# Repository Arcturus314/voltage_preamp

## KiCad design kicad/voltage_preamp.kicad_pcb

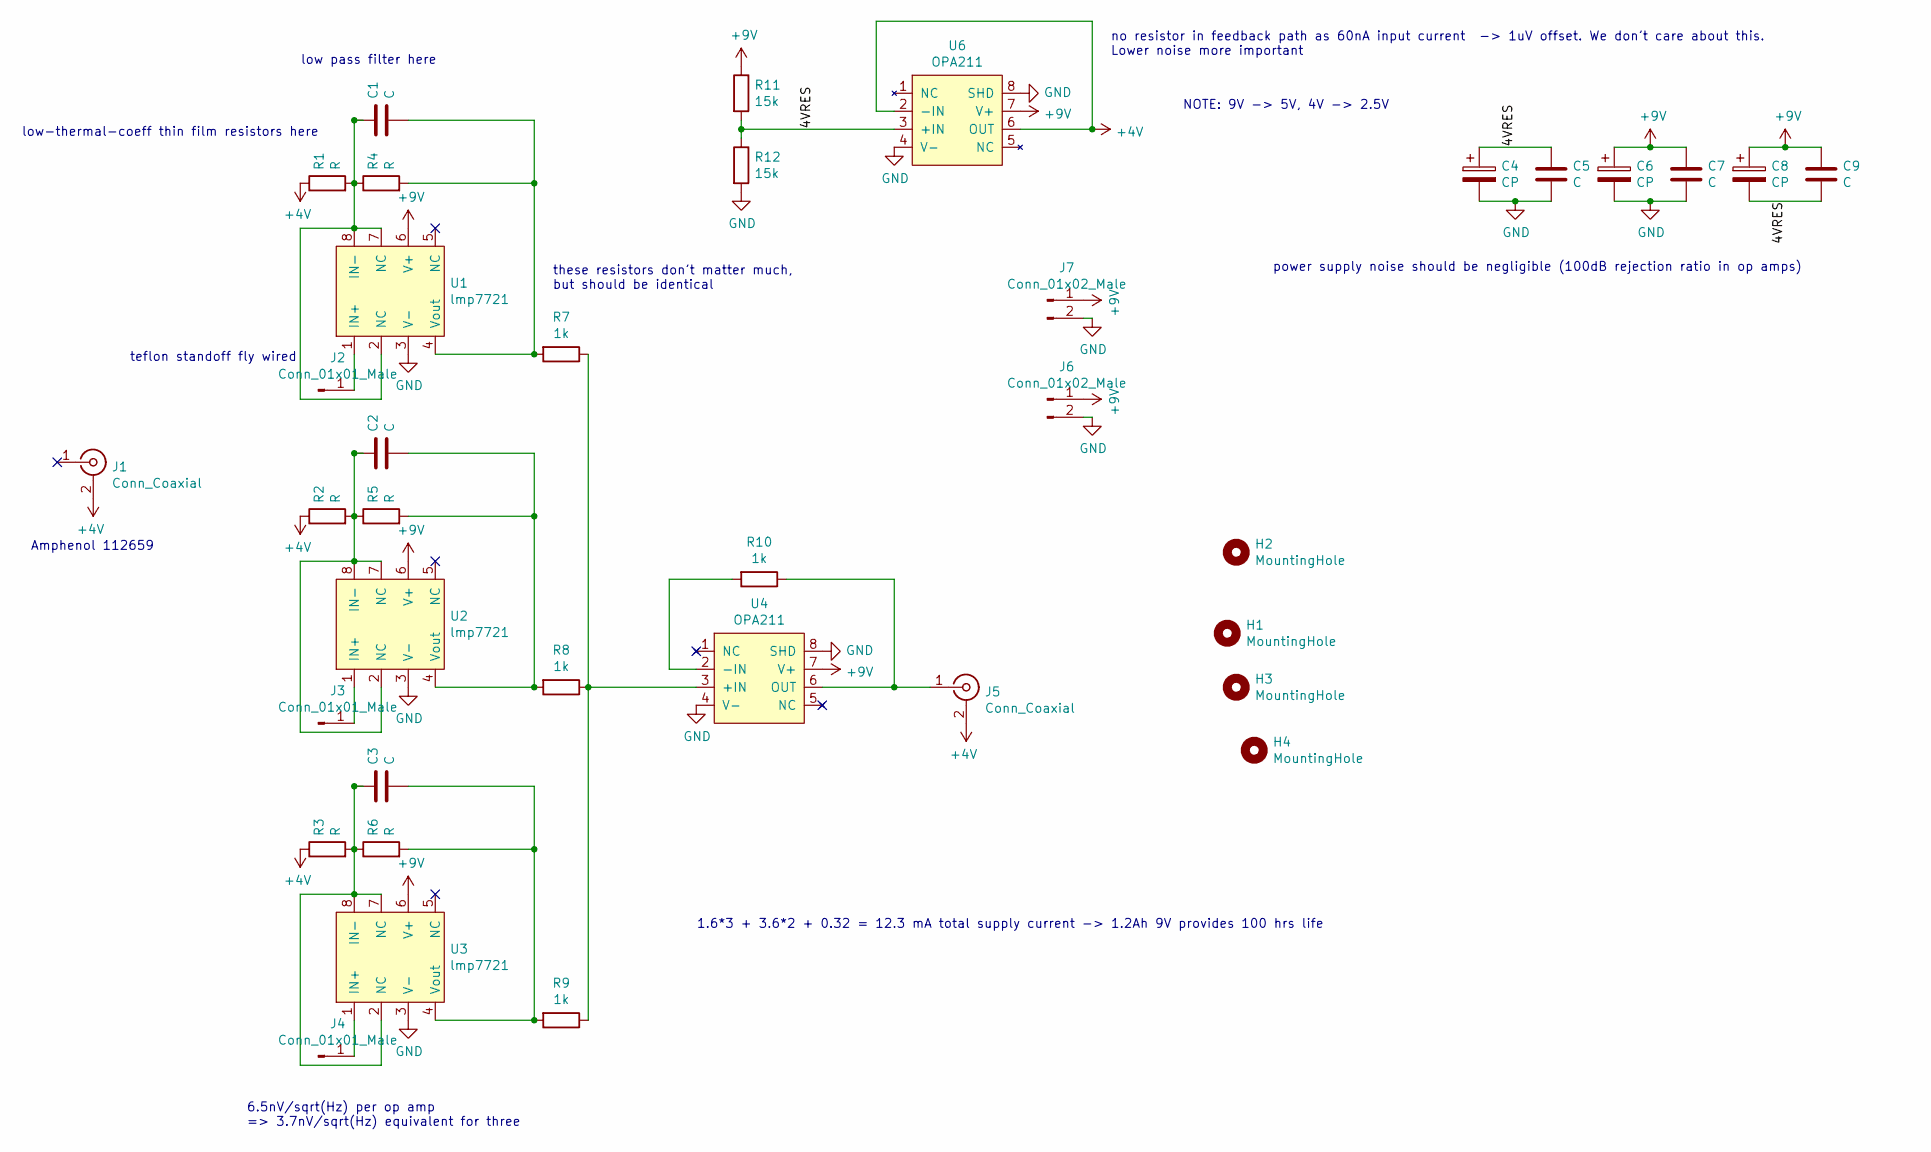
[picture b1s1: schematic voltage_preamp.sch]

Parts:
C1, C2, C3, C5, C7, C9: C; C_0805_2012Metric_Pad1.15x1.40mm_HandSolder
C4, C6, C8: CP; PinHeader_1x02_P2.54mm_Vertical
H1, H3, H4: MountingHole; MountingHole_3.2mm_M3
H2: MountingHole; MountingHole_3.2mm_M3_DIN965
J1, J5: Conn_Coaxial; BNC_Amphenol_B6252HB-NPP3G-50_Horizontal
J2, J3, J4: Conn_01x01_Male; PinHeader_1x01_P2.54mm_Vertical
J6: Conn_01x02_Male; BatteryHolder_Keystone_2479_3xAAA
J7: Conn_01x02_Male; BNC_Amphenol_B6252HB-NPP3G-50_Horizontal
R1, R2, R3, R4, R5, R6: R; R_0805_2012Metric_Pad1.15x1.40mm_HandSolder
R7, R8, R9, R10: 1k; R_0805_2012Metric_Pad1.15x1.40mm_HandSolder
R11, R12: 15k; R_0805_2012Metric_Pad1.15x1.40mm_HandSolder
U1, U2, U3: lmp7721
U4, U6: OPA211; VSSOP-8_3.0x3.0mm_P0.65mm

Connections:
+4V: J1.2 (Ext), J5.2 (Ext), R1.1, R2.1, R3.1, U6.2 (-IN), U6.6 (OUT)
+9V: C6.1, C7.1, C8.1, C9.1, J6.1, J7.1, R11.1, U1.6 (V+), U2.6 (V+), U3.6 (V+), U4.7 (V+), U6.7 (V+)
/4VRES: C4.1, C5.1, C8.2, C9.2, R11.2, R12.1, U6.3 (+IN)
GND: C4.2, C5.2, C6.2, C7.2, J6.2, J7.2, R12.2, U1.3 (V-), U2.3 (V-), U3.3 (V-), U4.4 (V-), U4.8 (SHD), U6.4 (V-), U6.8 (SHD)
unnamed: C1.1, R1.2, R4.1, U1.2 (NC), U1.7 (NC), U1.8 (IN-)
unnamed: C1.2, R4.2, R7.2, U1.4 (Vout)
unnamed: C2.1, R2.2, R5.1, U2.2 (NC), U2.7 (NC), U2.8 (IN-)
unnamed: C2.2, R5.2, R8.2, U2.4 (Vout)
unnamed: C3.1, R3.2, R6.1, U3.2 (NC), U3.7 (NC), U3.8 (IN-)
unnamed: C3.2, R6.2, R9.2, U3.4 (Vout)
unnamed: J2.1, U1.1 (IN+)
unnamed: J3.1, U2.1 (IN+)
unnamed: J4.1, U3.1 (IN+)
unnamed: J5.1 (In), R10.1, U4.6 (OUT)
unnamed: R7.1, R8.1, R9.1, U4.3 (+IN)
unnamed: R10.2, U4.2 (-IN)

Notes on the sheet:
teflon standoff fly wired
low-thermal-coeff thin film resistors here
these resistors don't matter much, but should be identical
low pass filter here
power supply noise should be negligible (100dB rejection ratio in op amps)
6.5nV/sqrt(Hz) per op amp => 3.7nV/sqrt(Hz) equivalent for three
1.6*3 + 3.6*2 + 0.32 = 12.3 mA total supply current -> 1.2Ah 9V provides 100 hrs life
no resistor in feedback path as 60nA input current -> 1uV offset. We don’t care about this. Lower noise more important
NOTE: 9V -> 5V, 4V -> 2.5V
Amphenol 112659

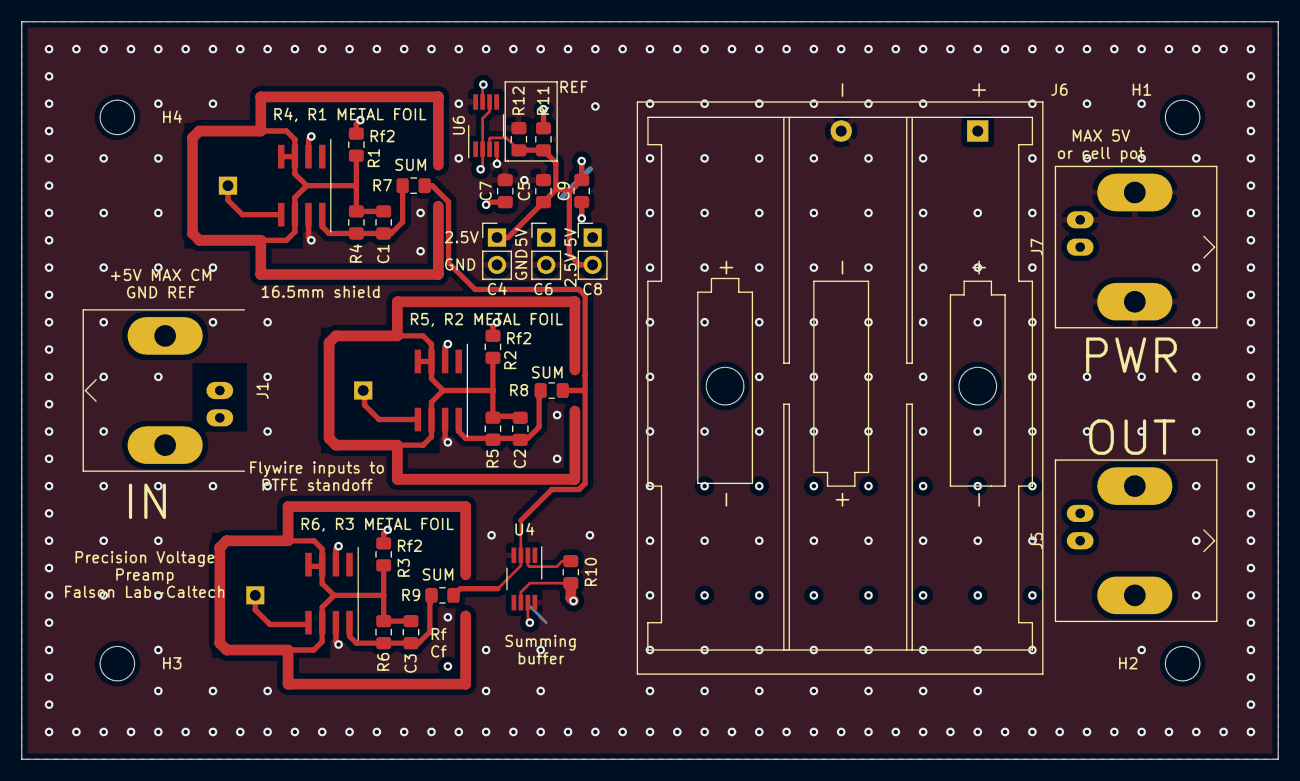
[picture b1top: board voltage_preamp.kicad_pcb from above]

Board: 4 copper layers, 116.8 x 68.6 mm, 37 parts (0 on the bottom side), 16 nets.

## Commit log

2021-05-04 wip design
2021-05-06 v1 schematic and layout complete, simulated
2021-05-06 fixed bypass cap network
2021-05-06 added comments
2021-05-08 now using 4.5V of AAA cells for power, power input available, SMAs for power input and output
2021-05-09 fixed via shielding, now using bnc as output and power connectors
